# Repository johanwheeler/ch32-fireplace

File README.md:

# Merry Christmas!

And a happy new year! Here you will find some instructions for the christmas card, as well as some technical details. 

https://github.com/johanwheeler/ch32-fireplace/assets/45564940/a2e65534-c451-412c-9a83-9337bf3cca4e

[Longer demo here](https://photos.app.goo.gl/RaVmtgkoQ25G9iBE6), [Short Hackaday article](https://hackaday.com/2024/01/02/an-animated-led-fireplace-powered-by-the-ch32v003/)

# Instructions

If your card has white plastic in front of the screen, remove the front plate and peel the film, then connect to any USB-C power source. The stockings above the fire are actually touch buttons! Press firmly to interact.

Sound: Toggle sound on or off. 

Next: Go to next animation.

Present: Call for santa. Remember that santa will only deliver presents at night ;)

# Technical details

For fellow nerds.

## Mechanical design

The initial shape was made in Fusion360, together with the grid and acrylic piece. The outlines were then imported into Inkscape, where the graphics were designed. To save ourselves a lot of work during the assembly process, we put an effort into minimizing part count as much as possible. We did this by combining multiple functions into one part, for example the middle PCB serves as decoration, diffuser for the LEDs, and also has buttons integrated. This way we managed to get all the looks and functionality with only 5 major mechanical components, saving us a lot of work when we eventually assembled all 50 of these.

## Electrical design

The main electrical components are:

 - CH32V003 RISC-V microcontroller
 - WS2812B (neopixel) LED matrix with 64 pixels
 - Buzzer for music and sound effects
 - Capacitive touch buttons
 - Photoresistor

These are distributed on 3 PCBs for a 3D effect, KiCAD was used to design the PCBs:

 - Back PCB has most of the components including MCU, Buzzer, LEDs, and programming headers.
 - Middle PCB has a USB-C port and capacitive buttons. Exposed FR-4 is used as a diffuser for the LEDs. 
 - Front PCB just looks nice.

## Assembly

The project is assembled in several steps that need to be followed in the correct order.

 - Components on back PCB.
 - Upload code (on back PCB).
 - Attach USB-C jack and grid on middle PCB.
 - Solder middle PCB to back PCB headers.
 - Attach acrylic on middle PCB.
 - Solder female headers on front PCB.
 - Attach front PCB.
 - Plug in and enjoy!

We got all of the back PCB smd components assembled by JLCPCB. We then set up a mini production line over the weekend and made 50 of these to give away to friends and family. The final cost came out to around 6$ per fireplace, manageable even with our student budgets. 

## Code

All code was written in plain C using the ch32v003fun dev environment and can be compiled using PlatformIO. The main code can be found in [src/main.c](SW/fireplace-PIO/src/main.c), and several peripheral drivers and functions can be found in the [lib](SW/fireplace-PIO/lib/) folder. The fire is procedurally generated, and the christmas tree has some math for the fading lights, otherwise the animations are stored frame by frame on the device. We really managed to squeeze a lot of functionality onto the 10 cent chip, with the code, animations and music filling up more than 90 percent of the 16k flash. 

# Contributions

This was a really fun project to do, and we learned a lot about small-scale production with limited budget and a tight deadline.

The people who made this:

 - Johan Wheeler (@johanwheeler): Electrical design, mechanical design, assembly.
 - Daniel Quach (@BasementCircuits): Project lead, electrical design, programming, animations, soldering.
 - Adam Anderson (@adaand00): Mechanical design, assembly, programming, animations. 

[See past years' cards!](https://github.com/Muoshy/christmas-cards)

Additional thanks to:

@CNLohr and contributors for the great resources in [ch32v003fun](https://github.com/cnlohr/ch32v003fun/tree/master).

CASE (Chalmers Autonomous Sytems and Electronics) for PCB shipping, tools, and workspace.

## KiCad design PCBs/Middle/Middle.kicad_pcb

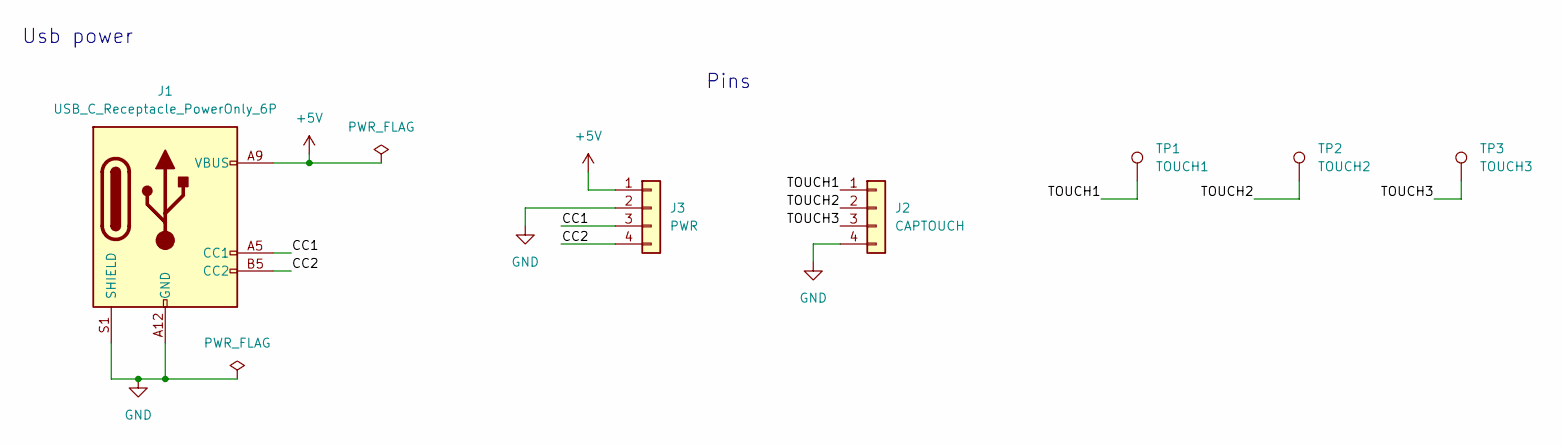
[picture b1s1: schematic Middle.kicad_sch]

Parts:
J1: USB_C_Receptacle_PowerOnly_6P; TYPE-C-31-D-08
J2: CAPTOUCH; PinHeader_1x04_P2.54mm_Vertical
J3: PWR; PinHeader_1x04_P2.54mm_Vertical
TP1: TOUCH1; cap_sock
TP2: TOUCH2; cap_sock
TP3: TOUCH3; cap_sock

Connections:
+5V: J1.A9 (VBUS), J1.B9 (VBUS), J3.1
/CC1: J1.A5 (CC1), J3.3
/CC2: J1.B5 (CC2), J3.4
/TOUCH1: J2.1, TP1.1
/TOUCH2: J2.2, TP2.1
/TOUCH3: J2.3, TP3.1
GND: J1.A12 (GND), J1.B12 (GND), J1.S1 (SHIELD), J2.4, J3.2

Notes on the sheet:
Usb power
Pins

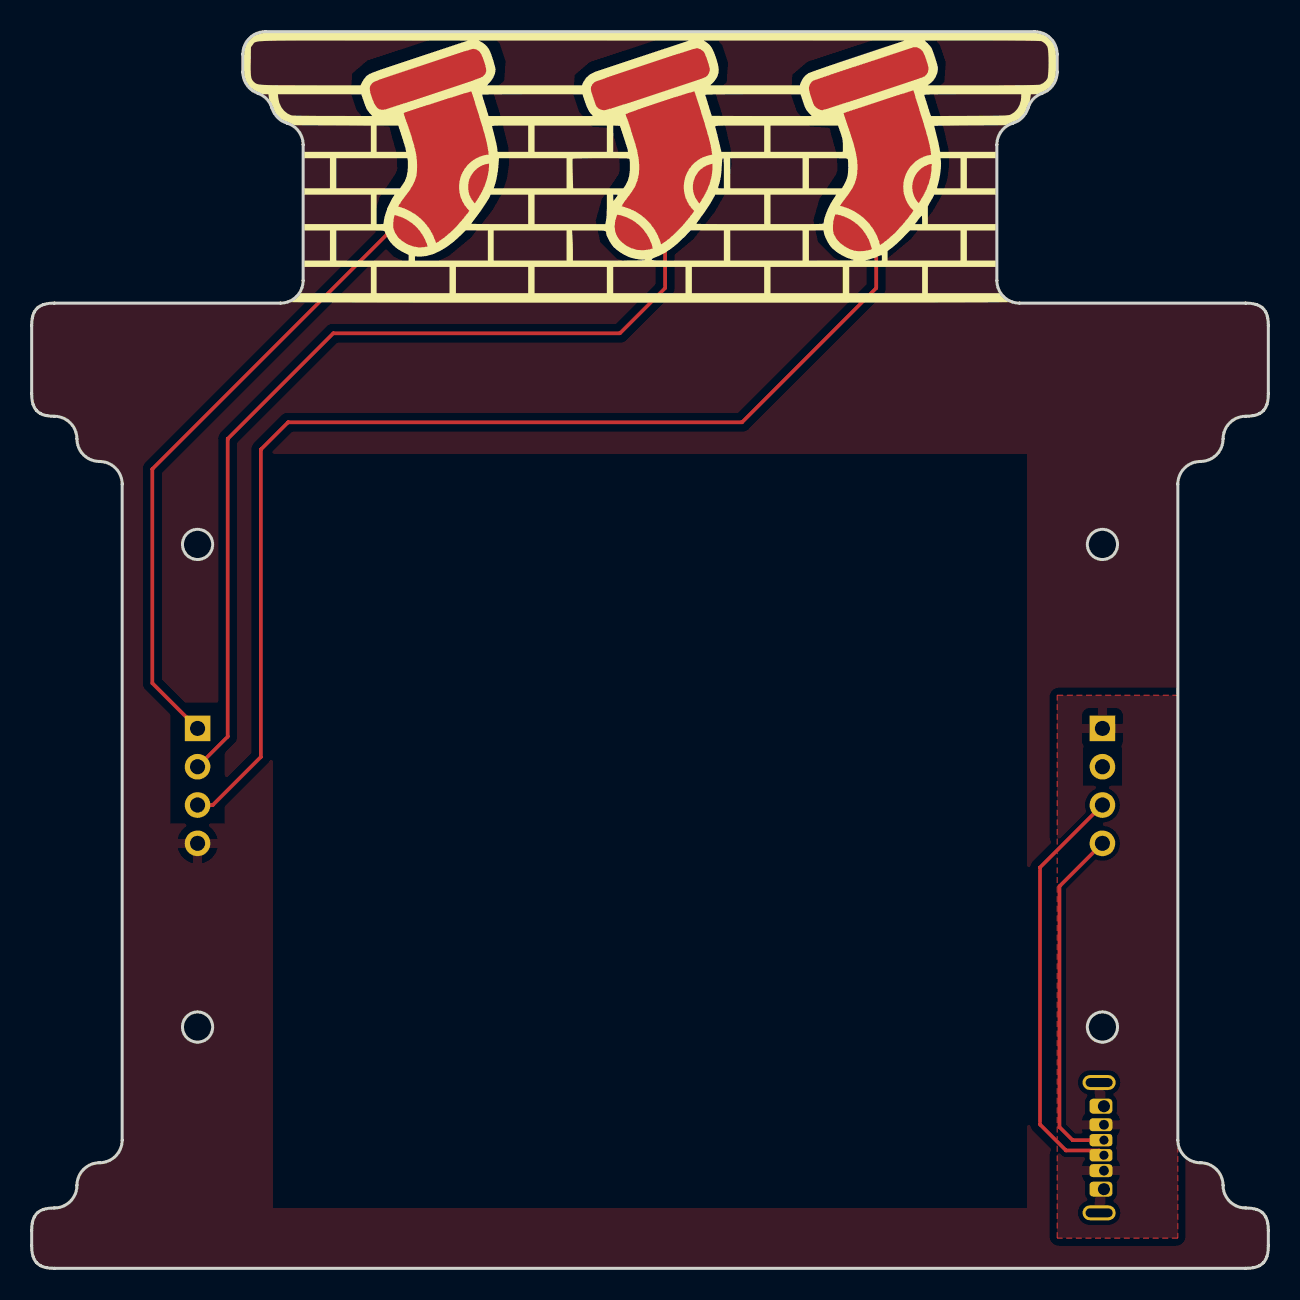
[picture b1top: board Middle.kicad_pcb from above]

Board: 2 copper layers, 82.0 x 82.0 mm, 6 parts (1 on the bottom side), 7 nets.

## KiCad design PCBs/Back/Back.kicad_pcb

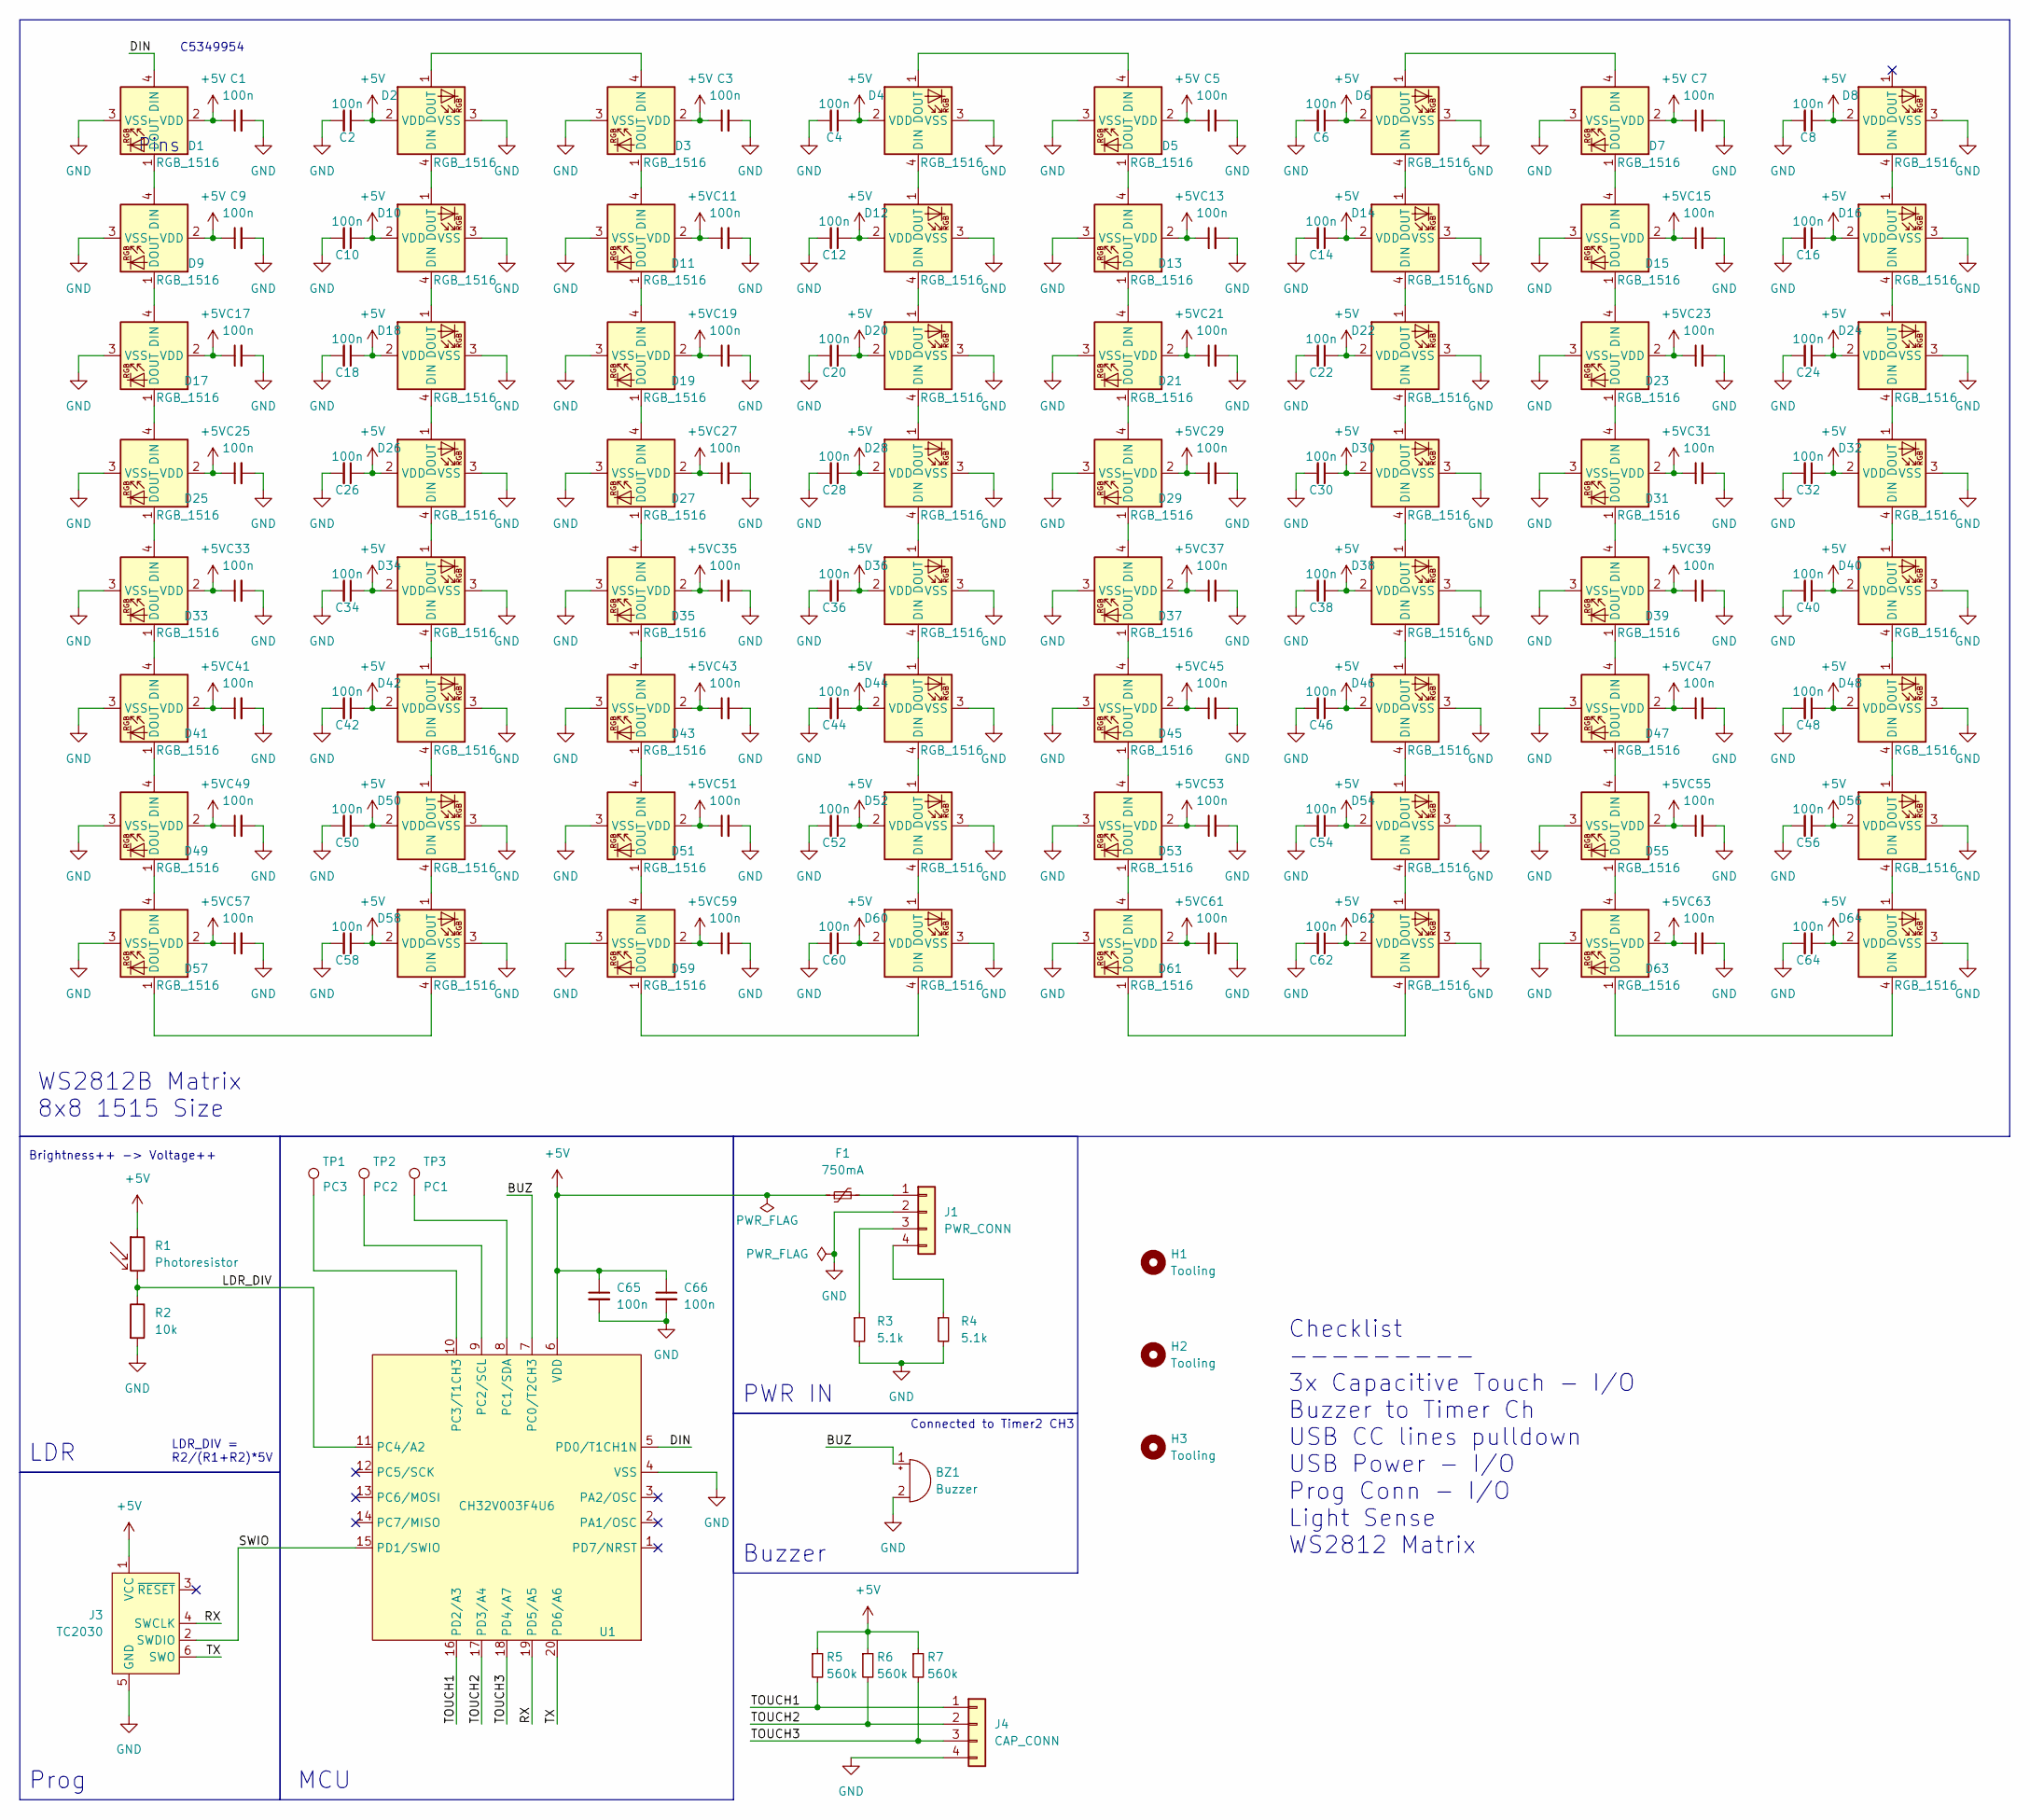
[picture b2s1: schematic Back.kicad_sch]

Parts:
BZ1: Buzzer; FUET-1325; MPN C391038; LCSC C391038
C1, C2, C3, C4, C5, C6, C7, C8, C9, C10, C11, C12, C13, C14, C15, C16, C17, C18, C19, C20, C21, C22, C23, C24, C25, C26, C27, C28, C29, C30, C31, C32, C33, C34, C35, C36, C37, C38, C39, C40, C41, C42, C43, C44, C45, C46, C47, C48, C49, C50, C51, C52, C53, C54, C55, C56, C57, C58, C59, C60, C61, C62, C63, C64, C65, C66: 100n; C_0402_1005Metric; MPN C1525; LCSC C1525
D1, D2, D3, D4, D5, D6, D7, D8, D9, D10, D11, D12, D13, D14, D15, D16, D17, D18, D19, D20, D21, D22, D23, D24, D25, D26, D27, D28, D29, D30, D31, D32, D33, D34, D35, D36, D37, D38, D39, D40, D41, D42, D43, D44, D45, D46, D47, D48, D49, D50, D51, D52, D53, D54, D55, D56, D57, D58, D59, D60, D61, D62, D63, D64: RGB_1516; XL-1615_WS2812B; MPN C5349954; LCSC C5349954
F1: 750mA; R_0805_2012Metric; MPN C269105; LCSC C269105
H1, H2, H3: Tooling; ToolingHole
J1: PWR_CONN; PinHeader_1x04_P2.54mm_Vertical
J3: TC2030; Tag-Connect_TC2030-IDC-NL_2x03_P1.27mm_Vertical
J4: CAP_CONN; PinHeader_1x04_P2.54mm_Vertical
R1: Photoresistor; GT36528; MPN C2904881; LCSC C2904881
R2: 10k; R_0603_1608Metric; MPN C25804; LCSC C25804
R3, R4: 5.1k; R_0603_1608Metric; MPN C23186; LCSC C23186
R5, R6, R7: 560k; R_0603_1608Metric; MPN C23203; LCSC C23203
TP1: PC3; TestPoint_Pad_D2.0mm
TP2: PC2; TestPoint_Pad_D2.0mm
TP3: PC1; TestPoint_Pad_D2.0mm
U1: CH32V003F4U6; QFN-20-1EP_3x3mm_P0.4mm_EP1.65x1.65mm; MPN C5299908; LCSC C5299908

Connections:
+5V: C1.1, C2.1, C3.1, C4.1, C5.1, C6.1, C7.1, C8.1, C9.1, C10.1, C11.1, C12.1, C13.1, C14.1, C15.1, C16.1, C17.1, C18.1, C19.1, C20.1, C21.1, C22.1, C23.1, C24.1, C25.1, C26.1, C27.1, C28.1, C29.1, C30.1, C31.1, C32.1, C33.1, C34.1, C35.1, C36.1, C37.1, C38.1, C39.1, C40.1, C41.1, C42.1, C43.1, C44.1, C45.1, C46.1, C47.1, C48.1, C49.1, C50.1, C51.1, C52.1, C53.1, C54.1, C55.1, C56.1, C57.1, C58.1, C59.1, C60.1, C61.1, C62.1, C63.1, C64.1, C65.1, C66.1, D1.2 (VDD), D2.2 (VDD), D3.2 (VDD), D4.2 (VDD), D5.2 (VDD), D6.2 (VDD), D7.2 (VDD), D8.2 (VDD), D9.2 (VDD), D10.2 (VDD), D11.2 (VDD), D12.2 (VDD), D13.2 (VDD), D14.2 (VDD), D15.2 (VDD), D16.2 (VDD), D17.2 (VDD), D18.2 (VDD), D19.2 (VDD), D20.2 (VDD), D21.2 (VDD), D22.2 (VDD), D23.2 (VDD), D24.2 (VDD), D25.2 (VDD), D26.2 (VDD), D27.2 (VDD), D28.2 (VDD), D29.2 (VDD), D30.2 (VDD), D31.2 (VDD), D32.2 (VDD), D33.2 (VDD), D34.2 (VDD), D35.2 (VDD), D36.2 (VDD), D37.2 (VDD), D38.2 (VDD), D39.2 (VDD), D40.2 (VDD), D41.2 (VDD), D42.2 (VDD), D43.2 (VDD), D44.2 (VDD), D45.2 (VDD), D46.2 (VDD), D47.2 (VDD), D48.2 (VDD), D49.2 (VDD), D50.2 (VDD), D51.2 (VDD), D52.2 (VDD), D53.2 (VDD), D54.2 (VDD), D55.2 (VDD), D56.2 (VDD), D57.2 (VDD), D58.2 (VDD), D59.2 (VDD), D60.2 (VDD), D61.2 (VDD), D62.2 (VDD), D63.2 (VDD), D64.2 (VDD), F1.1, J3.1 (VCC), R1.1, R5.1, R6.1, R7.1, U1.6 (VDD)
/BUZ: BZ1.1 (-), U1.7 (PC0/T2CH3)
/DIN: D1.4 (DIN), U1.5 (PD0/T1CH1N)
/LDR_DIV: R1.2, R2.1, U1.11 (PC4/A2)
/RX: J3.4 (SWCLK), U1.19 (PD5/A5)
/SWIO: J3.2 (SWDIO), U1.15 (PD1/SWIO)
/TOUCH1: J4.1, R5.2, U1.16 (PD2/A3)
/TOUCH2: J4.2, R6.2, U1.17 (PD3/A4)
/TOUCH3: J4.3, R7.2, U1.18 (PD4/A7)
/TX: J3.6 (SWO), U1.20 (PD6/A6)
GND: BZ1.2 (+), C1.2, C2.2, C3.2, C4.2, C5.2, C6.2, C7.2, C8.2, C9.2, C10.2, C11.2, C12.2, C13.2, C14.2, C15.2, C16.2, C17.2, C18.2, C19.2, C20.2, C21.2, C22.2, C23.2, C24.2, C25.2, C26.2, C27.2, C28.2, C29.2, C30.2, C31.2, C32.2, C33.2, C34.2, C35.2, C36.2, C37.2, C38.2, C39.2, C40.2, C41.2, C42.2, C43.2, C44.2, C45.2, C46.2, C47.2, C48.2, C49.2, C50.2, C51.2, C52.2, C53.2, C54.2, C55.2, C56.2, C57.2, C58.2, C59.2, C60.2, C61.2, C62.2, C63.2, C64.2, C65.2, C66.2, D1.3 (VSS), D2.3 (VSS), D3.3 (VSS), D4.3 (VSS), D5.3 (VSS), D6.3 (VSS), D7.3 (VSS), D8.3 (VSS), D9.3 (VSS), D10.3 (VSS), D11.3 (VSS), D12.3 (VSS), D13.3 (VSS), D14.3 (VSS), D15.3 (VSS), D16.3 (VSS), D17.3 (VSS), D18.3 (VSS), D19.3 (VSS), D20.3 (VSS), D21.3 (VSS), D22.3 (VSS), D23.3 (VSS), D24.3 (VSS), D25.3 (VSS), D26.3 (VSS), D27.3 (VSS), D28.3 (VSS), D29.3 (VSS), D30.3 (VSS), D31.3 (VSS), D32.3 (VSS), D33.3 (VSS), D34.3 (VSS), D35.3 (VSS), D36.3 (VSS), D37.3 (VSS), D38.3 (VSS), D39.3 (VSS), D40.3 (VSS), D41.3 (VSS), D42.3 (VSS), D43.3 (VSS), D44.3 (VSS), D45.3 (VSS), D46.3 (VSS), D47.3 (VSS), D48.3 (VSS), D49.3 (VSS), D50.3 (VSS), D51.3 (VSS), D52.3 (VSS), D53.3 (VSS), D54.3 (VSS), D55.3 (VSS), D56.3 (VSS), D57.3 (VSS), D58.3 (VSS), D59.3 (VSS), D60.3 (VSS), D61.3 (VSS), D62.3 (VSS), D63.3 (VSS), D64.3 (VSS), J1.2, J3.5 (GND), J4.4, R2.2, R3.2, R4.2, U1.4 (VSS), U1.21 (VSS)
unnamed: D1.1 (DOUT), D9.4 (DIN)
unnamed: D2.1 (DOUT), D3.4 (DIN)
unnamed: D4.1 (DOUT), D5.4 (DIN)
unnamed: D6.1 (DOUT), D7.4 (DIN)
unnamed: D10.4 (DIN), D18.1 (DOUT)
unnamed: D2.4 (DIN), D10.1 (DOUT)
unnamed: D3.1 (DOUT), D11.4 (DIN)
unnamed: D11.1 (DOUT), D19.4 (DIN)
unnamed: D12.4 (DIN), D20.1 (DOUT)
unnamed: D4.4 (DIN), D12.1 (DOUT)
unnamed: D5.1 (DOUT), D13.4 (DIN)
unnamed: D13.1 (DOUT), D21.4 (DIN)
unnamed: D14.4 (DIN), D22.1 (DOUT)
unnamed: D6.4 (DIN), D14.1 (DOUT)
unnamed: D7.1 (DOUT), D15.4 (DIN)
unnamed: D15.1 (DOUT), D23.4 (DIN)
unnamed: D16.4 (DIN), D24.1 (DOUT)
unnamed: D8.4 (DIN), D16.1 (DOUT)
unnamed: D9.1 (DOUT), D17.4 (DIN)
unnamed: D17.1 (DOUT), D25.4 (DIN)
unnamed: D18.4 (DIN), D26.1 (DOUT)
unnamed: D19.1 (DOUT), D27.4 (DIN)
unnamed: D20.4 (DIN), D28.1 (DOUT)
unnamed: D21.1 (DOUT), D29.4 (DIN)
unnamed: D22.4 (DIN), D30.1 (DOUT)
unnamed: D23.1 (DOUT), D31.4 (DIN)
unnamed: D24.4 (DIN), D32.1 (DOUT)
unnamed: D25.1 (DOUT), D33.4 (DIN)
unnamed: D26.4 (DIN), D34.1 (DOUT)
unnamed: D27.1 (DOUT), D35.4 (DIN)
unnamed: D28.4 (DIN), D36.1 (DOUT)
unnamed: D29.1 (DOUT), D37.4 (DIN)
unnamed: D30.4 (DIN), D38.1 (DOUT)
unnamed: D31.1 (DOUT), D39.4 (DIN)
unnamed: D32.4 (DIN), D40.1 (DOUT)
unnamed: D33.1 (DOUT), D41.4 (DIN)
unnamed: D34.4 (DIN), D42.1 (DOUT)
unnamed: D35.1 (DOUT), D43.4 (DIN)
unnamed: D36.4 (DIN), D44.1 (DOUT)
unnamed: D37.1 (DOUT), D45.4 (DIN)
unnamed: D38.4 (DIN), D46.1 (DOUT)
unnamed: D39.1 (DOUT), D47.4 (DIN)
unnamed: D40.4 (DIN), D48.1 (DOUT)
unnamed: D41.1 (DOUT), D49.4 (DIN)
unnamed: D42.4 (DIN), D50.1 (DOUT)
unnamed: D43.1 (DOUT), D51.4 (DIN)
unnamed: D44.4 (DIN), D52.1 (DOUT)
unnamed: D45.1 (DOUT), D53.4 (DIN)
unnamed: D46.4 (DIN), D54.1 (DOUT)
unnamed: D47.1 (DOUT), D55.4 (DIN)
unnamed: D48.4 (DIN), D56.1 (DOUT)
unnamed: D49.1 (DOUT), D57.4 (DIN)
unnamed: D50.4 (DIN), D58.1 (DOUT)
unnamed: D51.1 (DOUT), D59.4 (DIN)
unnamed: D52.4 (DIN), D60.1 (DOUT)
unnamed: D53.1 (DOUT), D61.4 (DIN)
unnamed: D54.4 (DIN), D62.1 (DOUT)
unnamed: D55.1 (DOUT), D63.4 (DIN)
unnamed: D56.4 (DIN), D64.1 (DOUT)
unnamed: D57.1 (DOUT), D58.4 (DIN)
unnamed: D59.1 (DOUT), D60.4 (DIN)
unnamed: D61.1 (DOUT), D62.4 (DIN)
unnamed: D63.1 (DOUT), D64.4 (DIN)
unnamed: F1.2, J1.1
unnamed: J1.3, R3.1
unnamed: J1.4, R4.1
unnamed: TP3.1, U1.8 (PC1/SDA)
unnamed: TP2.1, U1.9 (PC2/SCL)
unnamed: TP1.1, U1.10 (PC3/T1CH3)

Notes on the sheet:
Checklist --------- 3x Capacitive Touch - I/O Buzzer to Timer Ch USB CC lines pulldown USB Power - I/O Prog Conn - I/O Light Sense WS2812 Matrix
Pins
MCU
PWR IN
Connected to Timer2 CH3
WS2812B Matrix 8x8 1515 Size
Prog
Brightness++ -> Voltage++
Buzzer
LDR_DIV = R2/(R1+R2)*5V
LDR
C5349954

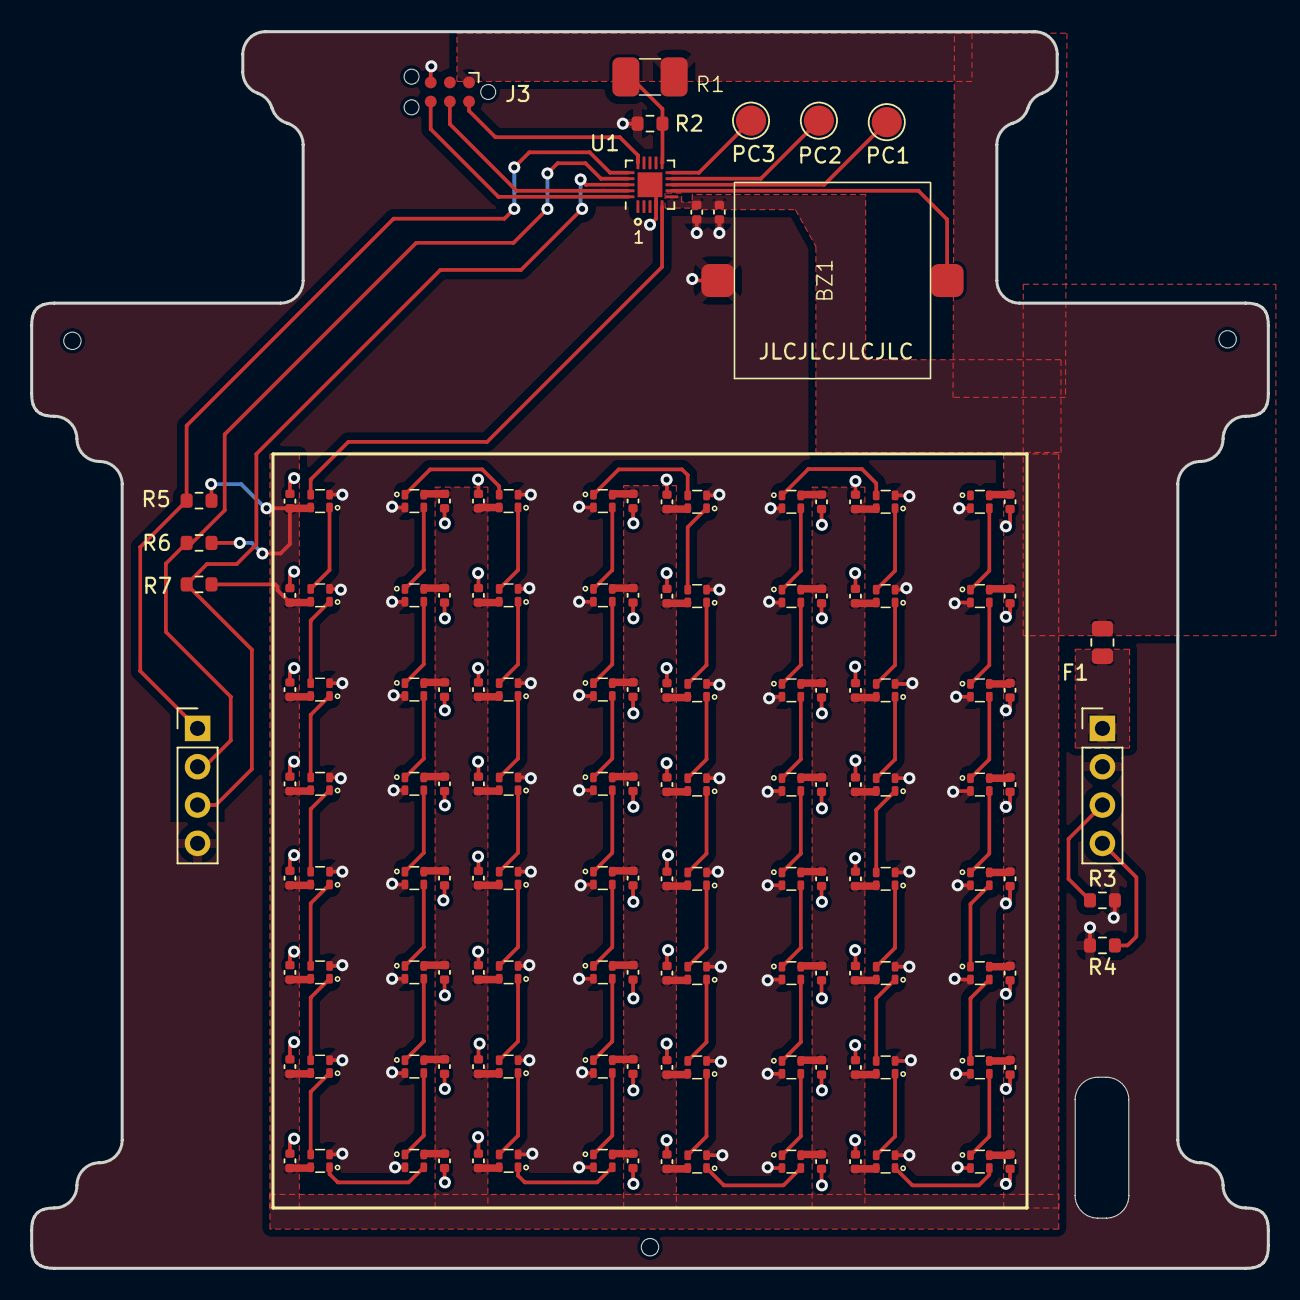
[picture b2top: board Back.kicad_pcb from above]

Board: 2 copper layers, 82.0 x 82.0 mm, 149 parts (0 on the bottom side), 80 nets.

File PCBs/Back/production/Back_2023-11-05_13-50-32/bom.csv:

Designator,Footprint,Quantity,Value,LCSC Part #
BZ1,FUET-1325,1,Buzzer,C391038
"C1, C10, C11, C12, C13, C14, C15, C16, C17, C18, C19, C2, C20, C21, C22, C23, C24, C25, C26, C27, C28, C29, C3, C30, C31, C32, C33, C34, C35, C36, C37, C38, C39, C4, C40, C41, C42, C43, C44, C45, C46, C47, C48, C49, C5, C50, C51, C52, C53, C54, C55, C56, C57, C58, C59, C6, C60, C61, C62, C63, C64, C65, C66, C7, C8, C9",0402,66,100n,C1525
"D1, D10, D11, D12, D13, D14, D15, D16, D17, D18, D19, D2, D20, D21, D22, D23, D24, D25, D26, D27, D28, D29, D3, D30, D31, D32, D33, D34, D35, D36, D37, D38, D39, D4, D40, D41, D42, D43, D44, D45, D46, D47, D48, D49, D5, D50, D51, D52, D53, D54, D55, D56, D57, D58, D59, D6, D60, D61, D62, D63, D64, D7, D8, D9",XL-1615_WS2812B,64,RGB_1516,C5349954
F1,0805,1,750mA,C269105
"H1, H2, H3",ToolingHole,3,Tooling,
J1,PinHeader_1x04_P2.54mm_Vertical,1,PWR_CONN,
J4,PinHeader_1x04_P2.54mm_Vertical,1,CAP_CONN,
R1,GT36528,1,Photoresistor,C2904881
R2,0603,1,10k,C31850
"R3, R4",0603,2,5.1k,C23186
"R5, R6, R7",0603,3,560k,C23203
TP1,TestPoint_Pad_D2.0mm,1,PC3,
TP2,TestPoint_Pad_D2.0mm,1,PC2,
TP3,TestPoint_Pad_D2.0mm,1,PC1,
U1,QFN-20-1EP_3x3mm_P0.4mm_EP1.65x1.65mm,1,CH32V003F4U6,C5299908

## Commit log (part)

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2023-10-28 Start on back PCB
2023-10-28 added some bitmaps
2023-10-28 Add gitignore for kicad
2023-10-28 Add ch32 component
2023-10-28 added ws2812 test
2023-10-28 Added WS2812b
2023-10-28 Back Outline
2023-10-28 Add outlines to PCBs
2023-10-28 Add USB to mid
2023-10-28 USB-C contact added to mid
2023-10-28 update back schem
2023-10-29 Updated back schematic
2023-10-29 Start on front silks
2023-10-31 Back schematic finished
2023-11-01 Front silks
2023-11-01 Middle silks
2023-11-04 back layout done
2023-11-04 Middle pcb done
2023-11-04 3D models
2023-11-04 Captivate sock
2023-11-04 Changed copper fill
2023-11-04 front pcb done
2023-11-04 fixed step files
2023-11-04 fixed usb-c cutout
2023-11-04 adjusted usb-c cutout
2023-11-05 Almost final adjustments
2023-11-05 Added dxf
2023-11-05 Order num place and gerbers for front
2023-11-05 Added small instruction text
2023-11-05 Socks with letters version
2023-11-05 Adjusted icons
2023-11-05 production files for back pcb
2023-11-05 gerbers for middle pcb
2023-11-24 Compiling
2023-11-24 Add SystemInit()
2023-11-24 Submodule added
2023-11-26 Playing Feliz Navidad!
2023-11-26 IRQ disable, buzzer tone()
2023-11-26 Cleaned up buzzer code
2023-11-26 Added adc function
2023-11-26 Added adc read example and fixed printf
2023-12-01 Buttons added
2023-12-01 main loop tweak
2023-12-01 Rework screen driver
2023-12-02 added jumping santa animation
2023-12-03 Added 4 sprite animations
    santa, present, reindeer, snowman
2023-12-04 State machine logic
2023-12-04 Without symbols
2023-12-05 Updated grid and acrylic
2023-12-06 Initial fire
2023-12-06 Procedural fire!
2023-12-06 Flip fire
2023-12-07 Tune fire parameters
2023-12-07 Added music change and mute functions
2023-12-07 Minor cleanup
2023-12-07 added reindeer + snowman snow
2023-12-07 more frames
2023-12-09 bugfix
2023-12-09 change brown for reindeer
2023-12-09 Matlab script for fire colors
2023-12-09 Buttons working (?)
2023-12-09 buzzer mute fix, wavetable, new tree
2023-12-09 Tune button thresholds
2023-12-09 New 3d prints
2023-12-09 Added tree fade + new wavetable
2023-12-09 Set fire seed
2023-12-09 Add no_present
2023-12-09 Santa peeking down
2023-12-09 Robust button measurement
2023-12-09 Add random in lib
2023-12-09 Fire change random source
2023-12-09 Add present
2023-12-09 added "cracking fire sound" to buzzer
2023-12-09 Integrate crackling
2023-12-09 fixed snowman jazzhands frames
2023-12-09 New snowman
2023-12-10 Remove old files
2023-12-10 Buzzer tune
2023-12-10 Add present opening
2023-12-10 Pogo_programming block
2023-12-10 pogo_programming
2023-12-10 Add more songs
2023-12-10 keep mute while changing song
2023-12-10 Change song for present
2023-12-10 Final code
2023-12-11 Add more images
2023-12-11 Add demo video
2023-12-11 Cleaned up schematic and generated pdfs
2023-12-11 Picture of mid PCB being soldered with jig
2023-12-22 Add link to longer demo
2024-01-21 Changed gitignore to include bom and placement files
2024-01-21 Added bom and placement files
2024-02-28 Added hackaday link
